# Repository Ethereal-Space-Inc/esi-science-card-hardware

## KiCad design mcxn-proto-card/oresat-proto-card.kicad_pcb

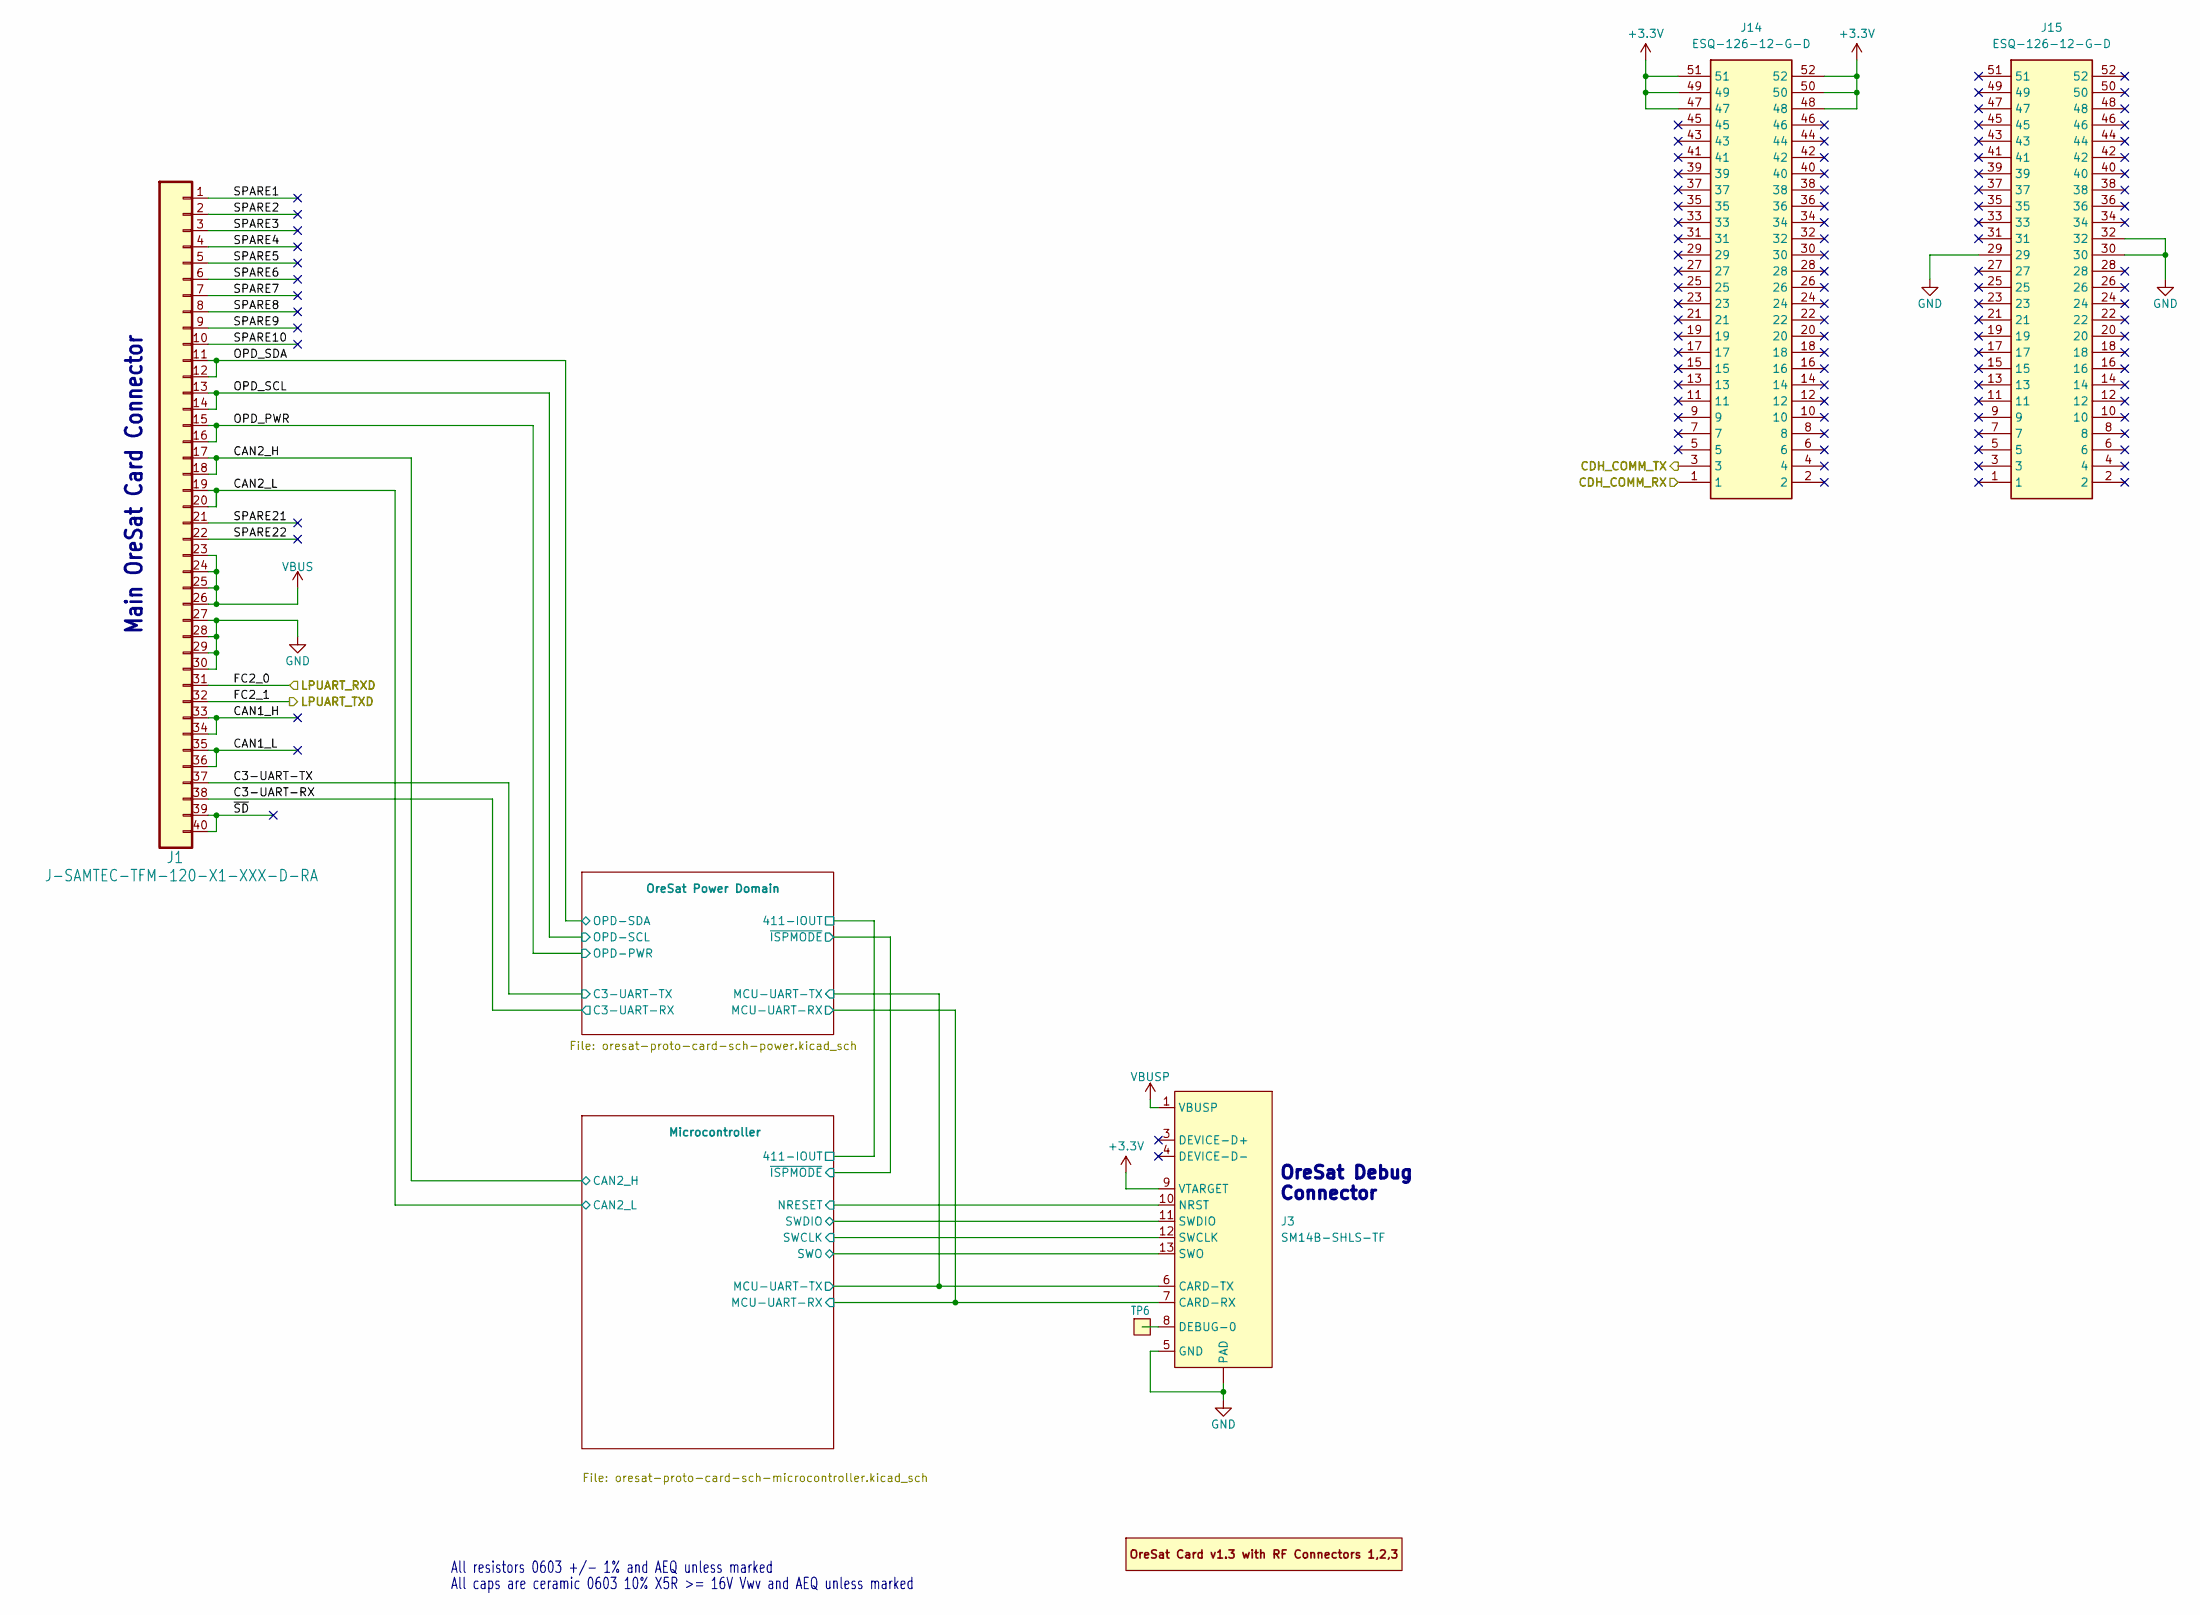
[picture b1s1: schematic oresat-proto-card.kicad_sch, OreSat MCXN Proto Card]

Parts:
J1: J-SAMTEC-TFM-120-X1-XXX-D-RA; MPN TFM-120-01-L-D-RA
J3: SM14B-SHLS-TF; J-JST-SM14BSHLSTF; MPN SM14B-SHLS-TF
J14, J15: ESQ-126-12-G-D; ESQ-126-Y-X-D; Mouser Part Number 200-ESQ12612GD
PCB1: ORESAT-CARD-V1.3-3RF; MPN oresat-proto-card-v6.0-2025-12-28
TP6: Test-Point; TestPoint-0.75mm-th

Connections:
+3.3V: J3.9 (VTARGET), J14.47, J14.48, J14.49, J14.50, J14.51, J14.52; also elsewhere on the board
/C3-UART-RX: J1.38; also elsewhere on the board
/C3-UART-TX: J1.37; also elsewhere on the board
/CAN1_H: J1.33, J1.34; also elsewhere on the board
/CAN1_L: J1.35, J1.36; also elsewhere on the board
/CAN2_H: J1.17, J1.18; also elsewhere on the board
/CAN2_L: J1.19, J1.20; also elsewhere on the board
/Microcontroller/CDH_COMM_RX: J14.1; also elsewhere on the board
/Microcontroller/CDH_COMM_TX: J14.3; also elsewhere on the board
/Microcontroller/FC2_0: J1.31; also elsewhere on the board
/Microcontroller/FC2_1: J1.32; also elsewhere on the board
/Microcontroller/MCU-UART-RX: J3.7 (CARD-RX); also elsewhere on the board
/Microcontroller/MCU-UART-TX: J3.6 (CARD-TX); also elsewhere on the board
/Microcontroller/NRESET: J3.10 (NRST); also elsewhere on the board
/Microcontroller/SWCLK: J3.12 (SWCLK); also elsewhere on the board
/Microcontroller/SWDIO: J3.11 (SWDIO); also elsewhere on the board
/Microcontroller/SWO: J3.13 (SWO); also elsewhere on the board
/OPD_PWR: J1.15, J1.16; also elsewhere on the board
/OPD_SCL: J1.13, J1.14; also elsewhere on the board
/OPD_SDA: J1.11, J1.12; also elsewhere on the board
/SPARE1: J1.1; also elsewhere on the board
/SPARE2: J1.2; also elsewhere on the board
/SPARE3: J1.3; also elsewhere on the board
/SPARE4: J1.4; also elsewhere on the board
/SPARE5: J1.5; also elsewhere on the board
/SPARE6: J1.6; also elsewhere on the board
/SPARE7: J1.7; also elsewhere on the board
/SPARE8: J1.8; also elsewhere on the board
/SPARE9: J1.9; also elsewhere on the board
/SPARE10: J1.10; also elsewhere on the board
/SPARE21: J1.21; also elsewhere on the board
/SPARE22: J1.22; also elsewhere on the board
/~SD: J1.39, J1.40; also elsewhere on the board
GND: J1.27, J1.28, J1.29, J1.30, J3.5 (GND), J3.14 (GND), J3.15 (PAD), J3.16 (PAD), J15.29, J15.30, J15.32; also elsewhere on the board
unnamed: J3.8 (DEBUG-0), TP6.1 (1_1)
VBUS: J1.23, J1.24, J1.25, J1.26; also elsewhere on the board
VBUSP: J3.1 (VBUSP), J3.2 (VBUSP); also elsewhere on the board

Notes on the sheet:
All caps are ceramic 0603 10% X5R >= 16V Vwv and AEQ unless marked
All resistors 0603 +/- 1% and AEQ unless marked
OreSat Debug Connector
Main OreSat Card Connector

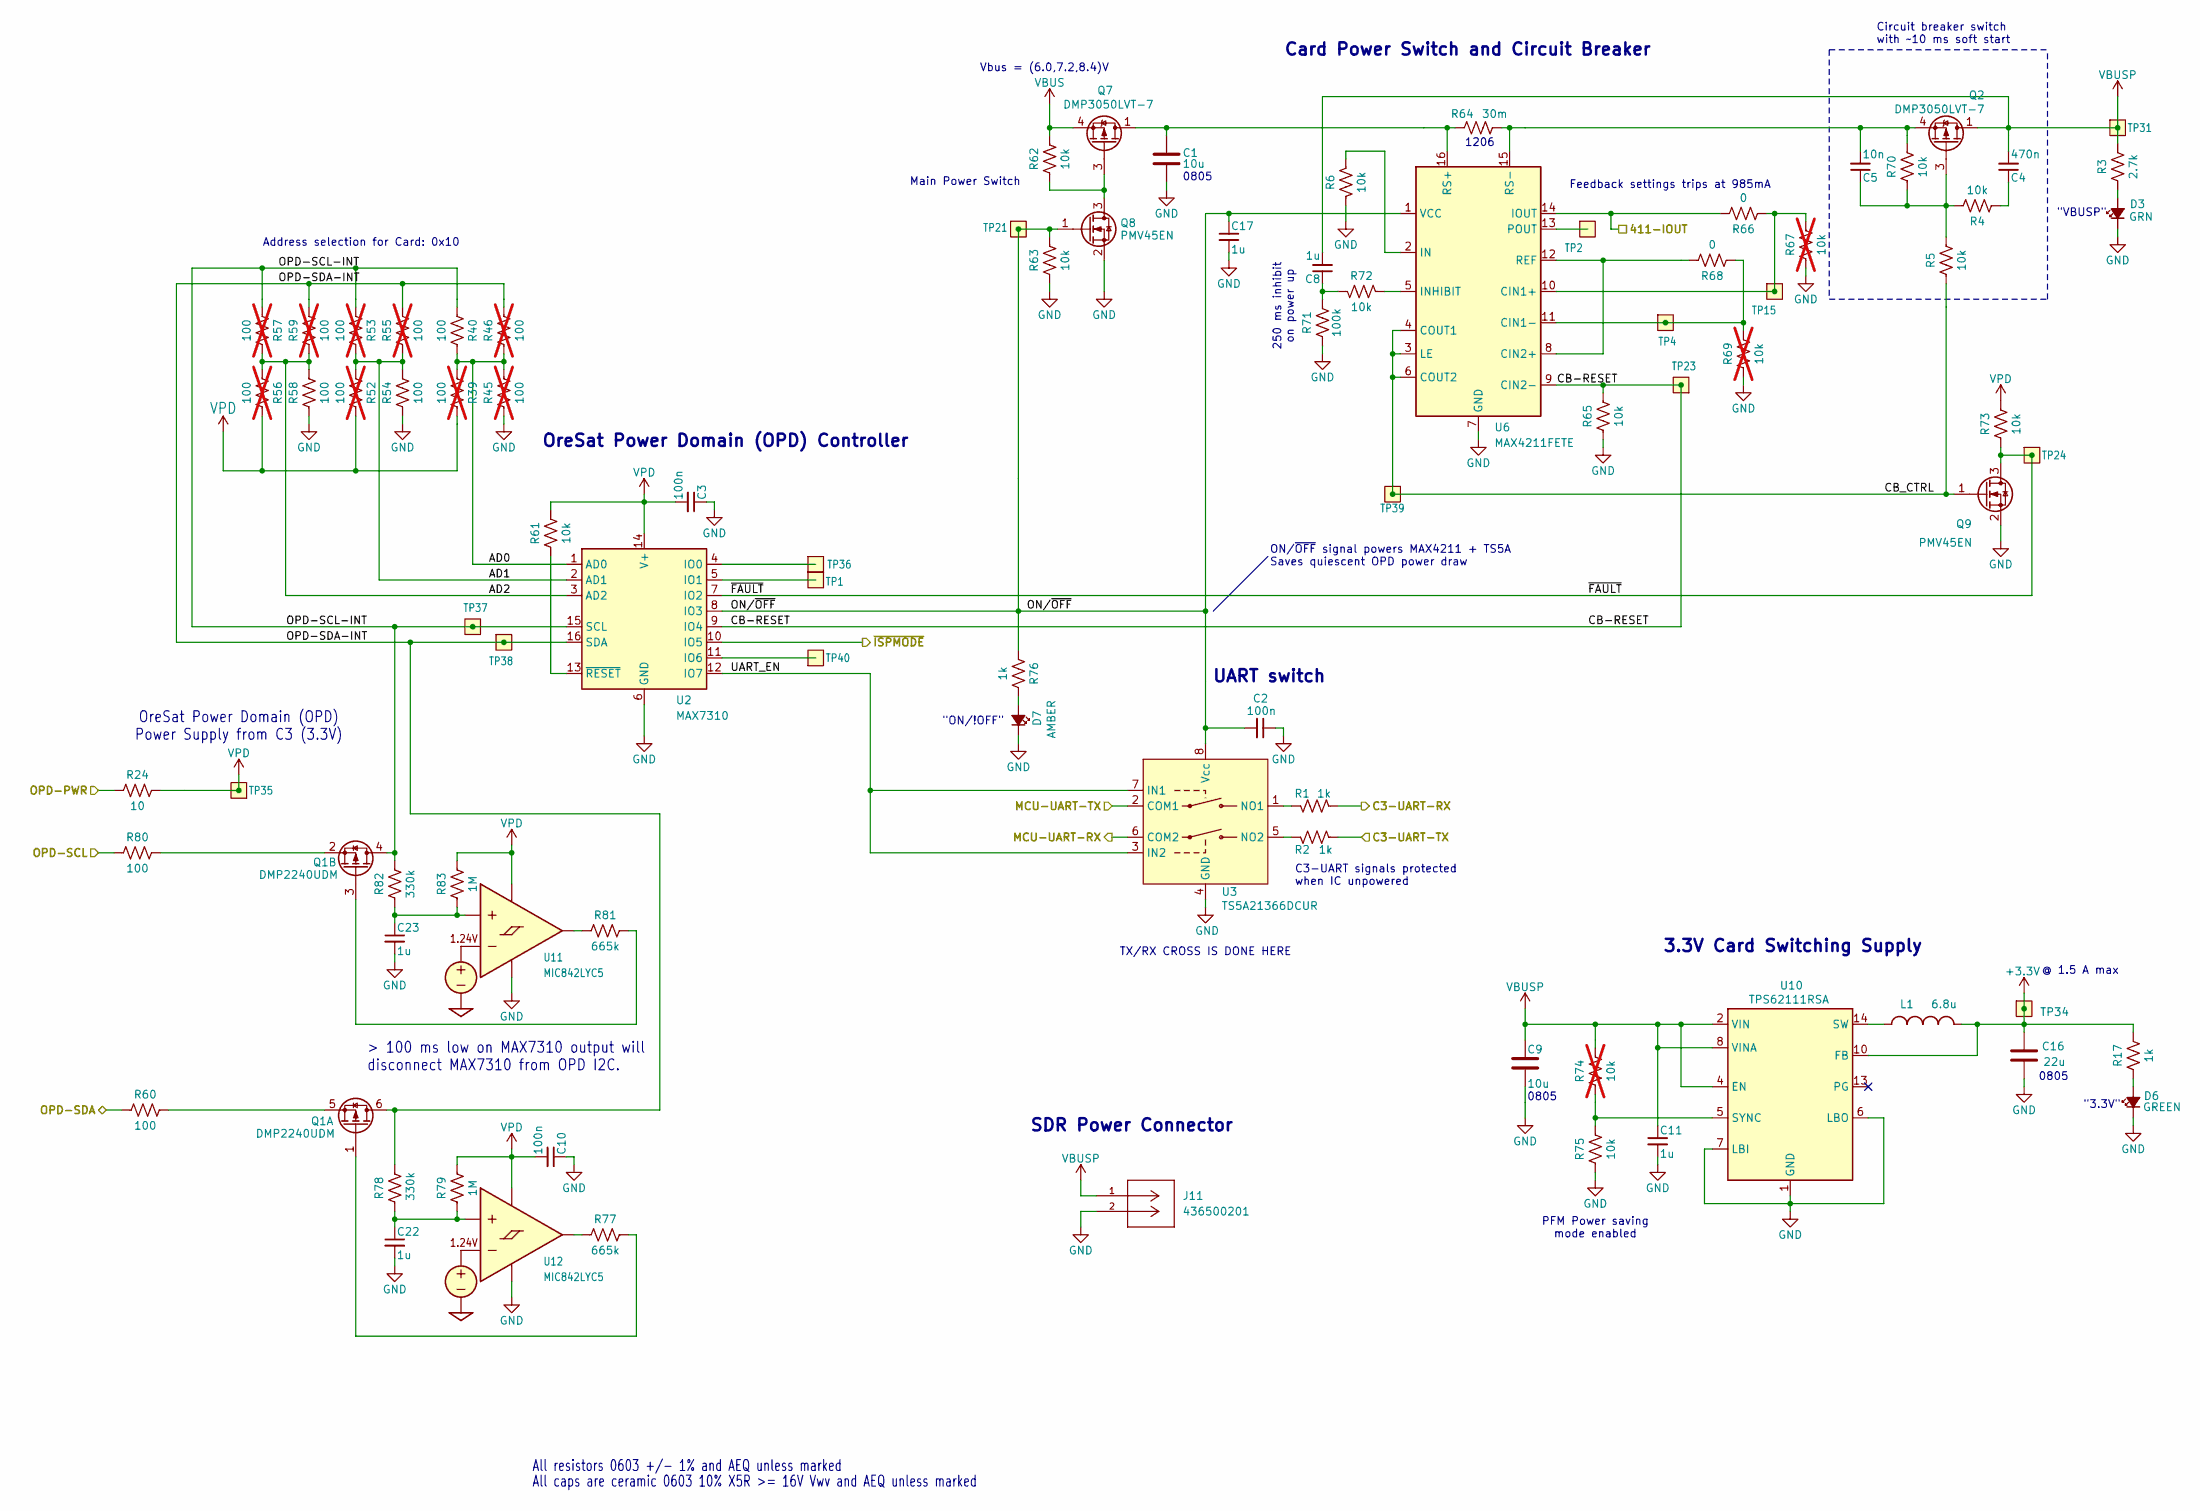
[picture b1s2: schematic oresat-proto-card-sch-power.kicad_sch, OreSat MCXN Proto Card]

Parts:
C1, C9: 10u; 0805-B-NOSILK; MPN GRT21BC71E106KE13K
C2, C3, C10: 100n; 0603-C-NOSILK; MPN C0603C104K5RACAUTO
C4: 470n; 0603-C-NOSILK; MPN C0603C474K3RACAUTO
C5: 10n; 0603-C-NOSILK; MPN C0603C103K5RACAUTO
C8, C11, C17, C22, C23: 1u; 0603-C-NOSILK; MPN GRT188R71E105KE13D
C16: 22u; 0805-C-NOSILK; MPN GRT21BC81C226ME13L
D3: GRN; LED_0603_1608Metric; MPN 150060GS75000
D6: GREEN; LED_0603_1608Metric; MPN 150060GS75000
D7: AMBER; LED_0603_1608Metric; MPN 150060AS75000
J11: 436500201; CONN_SD-43650-001_02_MOL; Manufacturer_Part_Number 436500201
L1: 6.8u; L_ECS-MPI4040; MPN ECS-MPI4040R4-6R8-R
Q1: DMP2240UDM; SOT-23-6; MPN DMP2240UDM
Q2, Q7: DMP3050LVT-7; TSOT-23-6; MPN DMP3050LVT-7
Q8, Q9: PMV45EN; SOT-23; MPN PMV45EN2R
R1, R2, R17, R76: 1k; 0603-C-NOSILK; MPN RMCF0603FT1K00
R3: 2.7k; 0603-C-NOSILK; MPN RMCF0603FT2K70
R4, R5, R6, R61, R62, R63, R65, R70, R72, R73, R75: 10k; 0603-C-NOSILK; MPN RMCF0603FT10K0
R24: 10; 0603-C-NOSILK; MPN RMCF0603FT10R0
R39, R45, R46, R52, R53, R55, R56, R57, R59: 100; 0603-C-NOSILK; MPN RMCF0603FT100R; not fitted
R40, R54, R58, R60, R80: 100; 0603-C-NOSILK; MPN RMCF0603FT100R
R64: 30m; R_1206_3216Metric; MPN CSR1206FK30L0
R66, R68: 0; 0603-C-NOSILK; MPN RMCF0603ZT0R00
R67, R69, R74: 10k; 0603-C-NOSILK; MPN RMCF0603FT10K0; not fitted
R71: 100k; 0603-C-NOSILK; MPN RMCF0603FT100K
R77, R81: 665k; 0603-C-NOSILK; MPN RMCF0603FT665K
R78, R82: 330k; 0603-C-NOSILK; MPN RMCF0603FT330K
R79, R83: 1M; 0603-C-NOSILK; MPN RMCF0603FT1M00
TP1, TP2, TP4, TP15, TP21, TP23, TP24, TP31, TP34, TP35, TP36, TP37, TP38, TP39, TP40: Test-Point; TestPoint-0.75mm-th
U2: MAX7310; QFN-16-1EP_4x4mm_P0.65mm_EP2.1x2.1mm; MPN MAX7310ATE
U3: TS5A21366DCUR; VSSOP-8_2.3x2mm_P0.5mm; MPN TS5A21366DCUR
U6: MAX4211FETE; QFN-16-1EP_4x4mm_P0.65mm_EP2.1x2.1mm; MPN MAX4211FETE
U10: TPS62111RSA; Texas_RSA_VQFN-16-1EP_4x4mm_P0.65mm_EP2.7x2.7mm; MPN TPS62111RSA
U11, U12: MIC842LYC5; SOT-353_SC-70-5; MPN MIC842LYC5-TR

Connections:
+3.3V: C16.1, L1.2, R17.2, TP34.1 (1_1), U10.10 (FB); also elsewhere on the board
/C3-UART-RX: R1.1; also elsewhere on the board
/C3-UART-TX: R2.1; also elsewhere on the board
/Microcontroller/411-IOUT: R66.2, U6.14 (IOUT); also elsewhere on the board
/Microcontroller/MCU-UART-RX: U3.6 (COM2); also elsewhere on the board
/Microcontroller/MCU-UART-TX: U3.2 (COM1); also elsewhere on the board
/Microcontroller/~ISPMODE: U2.10 (IO5); also elsewhere on the board
/OPD_PWR: R24.1; also elsewhere on the board
/OPD_SCL: R80.1; also elsewhere on the board
/OPD_SDA: R60.1; also elsewhere on the board
/OreSat Power Domain/AD0: R39.1, R40.2, R45.2, R46.1, U2.1 (AD0)
/OreSat Power Domain/AD1: R52.1, R53.2, R54.2, R55.1, U2.2 (AD1)
/OreSat Power Domain/AD2: R56.1, R57.2, R58.2, R59.1, U2.3 (AD2)
/OreSat Power Domain/CB-RESET: R65.2, TP23.1 (1_1), U2.9 (IO4), U6.9 (CIN2-)
/OreSat Power Domain/CB_CTRL: Q9.1 (G), R5.1, TP39.1 (1_1), U6.3 (LE), U6.4 (COUT1), U6.6 (COUT2)
/OreSat Power Domain/ON/~OFF: C2.2, C17.1, Q8.1 (G), R63.2, R76.1, TP21.1 (1_1), U2.8 (IO3), U3.8 (Vcc), U6.1 (VCC)
/OreSat Power Domain/OPD-SCL-INT: Q1.4 (D), R40.1, R53.1, R57.1, R82.2, TP37.1 (1_1), U2.15 (SCL)
/OreSat Power Domain/OPD-SDA-INT: Q1.6 (D), R46.2, R55.2, R59.2, R78.2, TP38.1 (1_1), U2.16 (SDA)
/OreSat Power Domain/UART_EN: U2.12 (IO7), U3.3 (IN2), U3.7 (IN1)
/OreSat Power Domain/~FAULT: Q9.3 (D), R73.1, TP24.1 (1_1), U2.7 (IO2)
GND: C1.2, C2.1, C3.1, C9.2, C10.1, C11.2, C16.2, C17.2, C22.2, C23.2, D3.1 (K), D6.1 (K), D7.1 (K), J11.2, Q8.2 (S), Q9.2 (S), R6.2, R45.1, R54.1, R58.1, R63.1, R65.1, R67.1, R69.1, R71.1, R75.1, U2.6 (GND), U2.17 (GND), U3.4 (GND), U6.7 (GND), U6.17 (GND), U10.1 (GND), U10.6 (LBO), U10.7 (LBI), U10.9 (GND), U10.11 (GND), U10.12 (GND), U10.16 (GND), U10.17 (GND), U11.2 (GND), U12.2 (GND); also elsewhere on the board
unnamed: C4.1, R4.1
unnamed: C8.1, R71.2, R72.2
unnamed: D3.2 (A), R3.1
unnamed: D6.2 (A), R17.1
unnamed: D7.2 (A), R76.2
unnamed: L1.1, U10.14 (SW), U10.15 (SW)
unnamed: Q1.1 (G), R77.2
unnamed: Q1.5 (S), R60.2
unnamed: Q1.3 (G), R81.2
unnamed: Q1.2 (S), R80.2
unnamed: C5.1, Q2.3 (G), R4.2, R5.2, R70.1
unnamed: C5.2, Q2.4 (S), R64.2, R70.2, U6.15 (RS-)
unnamed: Q7.3 (G), Q8.3 (D), R62.1
unnamed: TP36.1 (1_1), U2.4 (IO0)
unnamed: TP1.1 (1_1), U2.5 (IO1)
unnamed: TP40.1 (1_1), U2.11 (IO6)
unnamed: R61.1, U2.13 (~RESET)
unnamed: R1.2, U3.1 (NO1)
unnamed: R2.2, U3.5 (NO2)
unnamed: R66.1, R67.2, TP15.1 (1_1), U6.10 (CIN1+)
unnamed: R68.1, R69.2, TP4.1 (1_1), U6.11 (CIN1-)
unnamed: R68.2, U6.8 (CIN2+), U6.12 (REF)
unnamed: R6.1, U6.2 (IN)
unnamed: R72.1, U6.5 (INHIBIT)
unnamed: TP2.1 (1_1), U6.13 (POUT)
unnamed: C1.1, Q7.1 (D), Q7.2 (D), Q7.5 (D), Q7.6 (D), R64.1, U6.16 (RS+)
unnamed: R74.1, R75.2, U10.5 (SYNC)
unnamed: C23.1, R82.1, R83.1, U11.1 (INP)
unnamed: R81.1, U11.4 (OUT)
unnamed: C22.1, R78.1, R79.1, U12.1 (INP)
unnamed: R77.1, U12.4 (OUT)
VBUS: Q7.4 (S), R62.2; also elsewhere on the board
VBUSP: C4.2, C8.2, C9.1, C11.1, J11.1, Q2.1 (D), Q2.2 (D), Q2.5 (D), Q2.6 (D), R3.2, R74.2, TP31.1 (1_1), U10.2 (VIN), U10.3 (VIN), U10.4 (EN), U10.8 (VINA); also elsewhere on the board
VPD: C3.2, C10.2, R24.2, R39.2, R52.2, R56.2, R61.2, R73.2, R79.2, R83.2, TP35.1 (1_1), U2.14 (V+), U11.5 (VDD), U12.5 (VDD)

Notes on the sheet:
ON/~{OFF} signal powers MAX4211 + TS5A Saves quiescent OPD power draw
Feedback settings trips at 985mA
Card Power Switch and Circuit Breaker
1206
3.3V Card Switching Supply
"3.3V"
> 100 ms low on MAX7310 output will disconnect MAX7310 from OPD I2C.
SDR Power Connector
C3-UART signals protected when IC unpowered
OreSat Power Domain (OPD) Power Supply from C3 (3.3V)
Vbus = (6.0,7.2,8.4)V
All resistors 0603 +/- 1% and AEQ unless marked
0805
OreSat Power Domain (OPD) Controller
"VBUSP"
All caps are ceramic 0603 10% X5R >= 16V Vwv and AEQ unless marked
250 ms inhibit on power up
@ 1.5 A max
PFM Power saving mode enabled
"ON/!OFF"
TX/RX CROSS IS DONE HERE
Address selection for Card: 0x10
Circuit breaker switch with ~10 ms soft start
Main Power Switch
UART switch

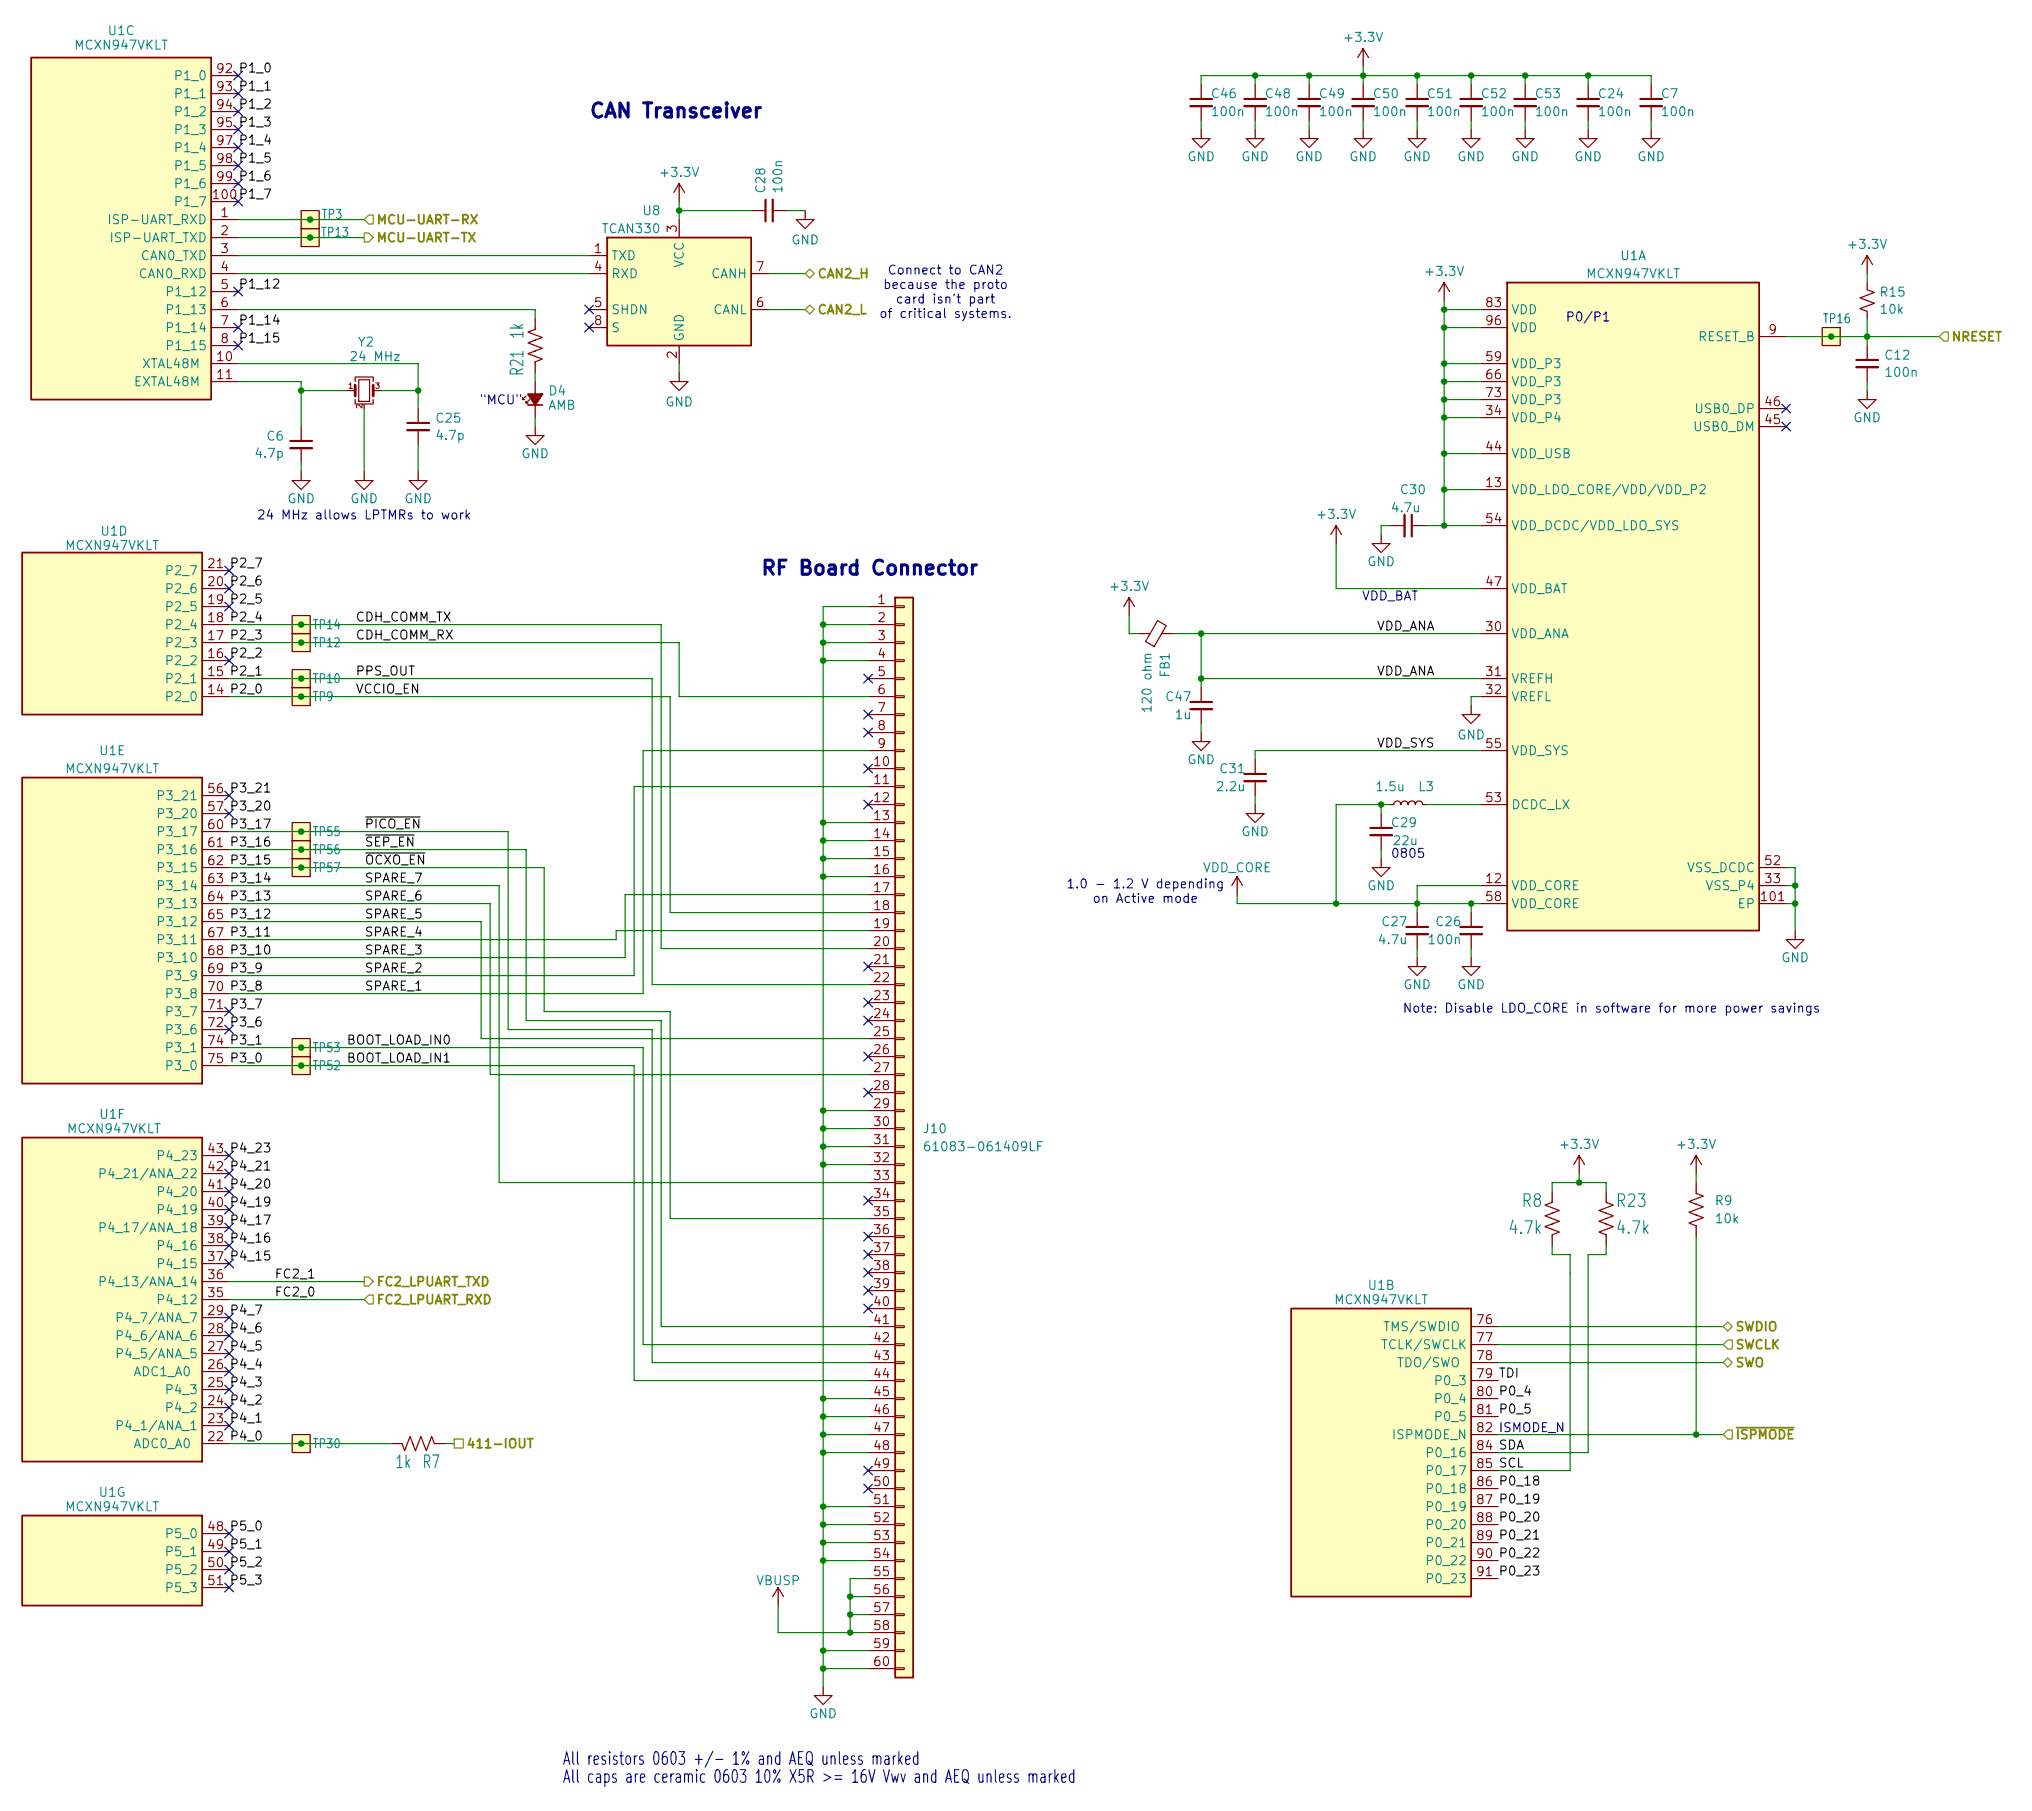
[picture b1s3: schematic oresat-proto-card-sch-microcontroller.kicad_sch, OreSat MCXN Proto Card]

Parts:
C6, C25: 4.7p; 0603-C-NOSILK; MPN C0603C479D5GACAUTO
C7, C12, C24, C26, C28, C46, C48, C49, C50, C51, C52, C53: 100n; 0603-C-NOSILK; MPN C0603C104K5RACAUTO
C27, C30: 4.7u; 0603-C-NOSILK; MPN EMK107BBJ475KAHT
C29: 22u; 0805-C-NOSILK; MPN GRT21BC81C226ME13L
C31: 2.2u; 0603-C-NOSILK; MPN GRT188C71E225KE13D
C47: 1u; 0603-C-NOSILK; MPN GRT188R71E105KE13D
D4: AMB; LED_0603_1608Metric; MPN 150060AS75000
FB1: 120 ohm; 0805-B-NOSILK; MPN 2508051217Y6
J10: 61083-061409LF; AMPHENOL_61083-061409LF
L3: 1.5u; L_0805_2012Metric; MPN SRP2012TMA-1R5M
R7, R21: 1k; 0603-C-NOSILK; MPN RMCF0603FT1K00
R8, R23: 4.7k; 0603-C-NOSILK; MPN RMCF0603FT4K70
R9, R15: 10k; 0603-C-NOSILK; MPN RMCF0603FT10K0
TP3, TP9, TP10, TP12, TP13, TP14, TP16, TP30, TP52, TP53, TP55, TP56, TP57: Test-Point; TestPoint-0.75mm-th
U1: MCXN947VKLT; MCXN947KVLT-QFP50P1600X1600X160-101N; MPN MCXN947VKLT
U8: TCAN330; SOT-23-8; MPN TCAN330DCNR
Y2: 24 MHz; Crystal_SMD_2016-4Pin_2.0x1.6mm; MPN 830108212309

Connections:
+3.3V: C7.1, C24.1, C28.1, C30.1, C46.1, C48.1, C49.1, C50.1, C51.1, C52.1, C53.1, FB1.1, R8.2, R9.2, R15.2, R23.2, U1.13 (VDD_LDO_CORE/VDD/VDD_P2), U1.34 (VDD_P4), U1.44 (VDD_USB), U1.47 (VDD_BAT), U1.54 (VDD_DCDC/VDD_LDO_SYS), U1.59 (VDD_P3), U1.66 (VDD_P3), U1.73 (VDD_P3), U1.83 (VDD), U1.96 (VDD), U8.3 (VCC); also elsewhere on the board
/CAN2_H: U8.7 (CANH); also elsewhere on the board
/CAN2_L: U8.6 (CANL); also elsewhere on the board
/Microcontroller/411-IOUT: R7.2; also elsewhere on the board
/Microcontroller/CDH_COMM_RX: J10.6, TP12.1 (1_1), U1.17 (P2_3); also elsewhere on the board
/Microcontroller/CDH_COMM_TX: J10.20, TP14.1 (1_1), U1.18 (P2_4); also elsewhere on the board
/Microcontroller/FC2_0: U1.35 (P4_12); also elsewhere on the board
/Microcontroller/FC2_1: U1.36 (P4_13/ANA_14); also elsewhere on the board
/Microcontroller/MCU-UART-RX: TP3.1 (1_1), U1.1 (ISP-UART_RXD); also elsewhere on the board
/Microcontroller/MCU-UART-TX: TP13.1 (1_1), U1.2 (ISP-UART_TXD); also elsewhere on the board
/Microcontroller/NRESET: C12.1, R15.1, TP16.1 (1_1), U1.9 (RESET_B); also elsewhere on the board
/Microcontroller/P0_4: U1.80 (P0_4)
/Microcontroller/P0_5: U1.81 (P0_5)
/Microcontroller/P0_18: U1.86 (P0_18)
/Microcontroller/P0_19: U1.87 (P0_19)
/Microcontroller/P0_20: U1.88 (P0_20)
/Microcontroller/P0_21: U1.89 (P0_21)
/Microcontroller/P0_22: U1.90 (P0_22)
/Microcontroller/P0_23: U1.91 (P0_23)
/Microcontroller/P1_0: U1.92 (P1_0)
/Microcontroller/P1_1: U1.93 (P1_1)
/Microcontroller/P1_2: U1.94 (P1_2)
/Microcontroller/P1_3: U1.95 (P1_3)
/Microcontroller/P1_4: U1.97 (P1_4)
/Microcontroller/P1_5: U1.98 (P1_5)
/Microcontroller/P1_6: U1.99 (P1_6)
/Microcontroller/P1_7: U1.100 (P1_7)
/Microcontroller/P1_12: U1.5 (P1_12)
/Microcontroller/P1_14: U1.7 (P1_14)
/Microcontroller/P1_15: U1.8 (P1_15)
/Microcontroller/P2_0: J10.18, TP9.1 (1_1), U1.14 (P2_0)
/Microcontroller/P2_1: J10.22, TP10.1 (1_1), U1.15 (P2_1)
/Microcontroller/P2_2: U1.16 (P2_2)
/Microcontroller/P2_5: U1.19 (P2_5)
/Microcontroller/P2_6: U1.20 (P2_6)
/Microcontroller/P2_7: U1.21 (P2_7)
/Microcontroller/P3_6: U1.72 (P3_6)
/Microcontroller/P3_7: U1.71 (P3_7)
/Microcontroller/P3_8: J10.9, U1.70 (P3_8)
/Microcontroller/P3_9: J10.11, U1.69 (P3_9)
/Microcontroller/P3_10: J10.17, U1.68 (P3_10)
/Microcontroller/P3_11: J10.19, U1.67 (P3_11)
/Microcontroller/P3_12: J10.25, U1.65 (P3_12)
/Microcontroller/P3_13: J10.27, U1.64 (P3_13)
/Microcontroller/P3_14: J10.33, U1.63 (P3_14)
/Microcontroller/P3_15: J10.35, TP57.1 (1_1), U1.62 (P3_15)
/Microcontroller/P3_16: J10.41, TP56.1 (1_1), U1.61 (P3_16)
/Microcontroller/P3_17: J10.43, TP55.1 (1_1), U1.60 (P3_17)
/Microcontroller/P3_20: U1.57 (P3_20)
/Microcontroller/P3_21: U1.56 (P3_21)
/Microcontroller/P4_0: R7.1, TP30.1 (1_1), U1.22 (ADC0_A0)
/Microcontroller/P4_1: U1.23 (P4_1/ANA_1)
/Microcontroller/P4_2: U1.24 (P4_2)
/Microcontroller/P4_3: U1.25 (P4_3)
/Microcontroller/P4_4: U1.26 (ADC1_A0)
/Microcontroller/P4_5: U1.27 (P4_5/ANA_5)
/Microcontroller/P4_6: U1.28 (P4_6/ANA_6)
/Microcontroller/P4_7: U1.29 (P4_7/ANA_7)
/Microcontroller/P4_15: U1.37 (P4_15)
/Microcontroller/P4_16: U1.38 (P4_16)
/Microcontroller/P4_17: U1.39 (P4_17/ANA_18)
/Microcontroller/P4_19: U1.40 (P4_19)
/Microcontroller/P4_20: U1.41 (P4_20)
/Microcontroller/P4_21: U1.42 (P4_21/ANA_22)
/Microcontroller/P4_23: U1.43 (P4_23)
/Microcontroller/P5_0: U1.48 (P5_0)
/Microcontroller/P5_1: U1.49 (P5_1)
/Microcontroller/P5_2: U1.50 (P5_2)
/Microcontroller/P5_3: U1.51 (P5_3)
/Microcontroller/SCL: R8.1, U1.85 (P0_17)
/Microcontroller/SDA: R23.1, U1.84 (P0_16)
/Microcontroller/SWCLK: U1.77 (TCLK/SWCLK); also elsewhere on the board
/Microcontroller/SWDIO: U1.76 (TMS/SWDIO); also elsewhere on the board
/Microcontroller/SWO: U1.78 (TDO/SWO); also elsewhere on the board
/Microcontroller/TDI: U1.79 (P0_3)
/Microcontroller/VDD_ANA: C47.1, FB1.2, U1.30 (VDD_ANA), U1.31 (VREFH)
/Microcontroller/VDD_SYS: C31.1, U1.55 (VDD_SYS)
/Microcontroller/~ISPMODE: R9.1, U1.82 (ISPMODE_N); also elsewhere on the board
GND: C6.2, C7.2, C12.2, C24.2, C25.2, C26.2, C27.2, C28.2, C29.2, C30.2, C31.2, C46.2, C47.2, C48.2, C49.2, C50.2, C51.2, C52.2, C53.2, D4.1 (K), J10.1, J10.2, J10.3, J10.4, J10.13, J10.14, J10.15, J10.16, J10.29, J10.30, J10.31, J10.32, J10.45, J10.46, J10.47, J10.48, J10.51, J10.52, J10.53, J10.54, J10.59, J10.60, U1.32 (VREFL), U1.33 (VSS_P4), U1.52 (VSS_DCDC), U1.101 (EP), U8.2 (GND), Y2.2 (G), Y2.4 (G); also elsewhere on the board
unnamed: D4.2 (A), R21.2
unnamed: L3.2, U1.53 (DCDC_LX)
unnamed: U1.3 (CAN0_TXD), U8.1 (TXD)
unnamed: U1.4 (CAN0_RXD), U8.4 (RXD)
unnamed: R21.1, U1.6 (P1_13)
unnamed: C25.1, U1.10 (XTAL48M), Y2.3
unnamed: C6.1, U1.11 (EXTAL48M), Y2.1
VBUSP: J10.55, J10.56, J10.57, J10.58; also elsewhere on the board
VDD_CORE: C26.1, C27.1, C29.1, L3.1, U1.12 (VDD_CORE), U1.58 (VDD_CORE)

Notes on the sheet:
Connect to CAN2 because the proto card isn't part of critical systems.
All caps are ceramic 0603 10% X5R >= 16V Vwv and AEQ unless marked
Note: Disable LDO_CORE in software for more power savings
All resistors 0603 +/- 1% and AEQ unless marked
24 MHz allows LPTMRs to work
0805
1.0 - 1.2 V depending on Active mode
VDD_BAT
"MCU"
P0/P1
ISMODE_N
RF Board Connector
CAN Transceiver

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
